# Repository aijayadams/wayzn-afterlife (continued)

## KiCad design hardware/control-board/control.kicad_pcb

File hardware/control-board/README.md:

# Phase B: wayzn-afterlife control board v1 (WYP-BC-100 replacement)

A drop-in replacement for the Wayzn WYP-BC-100 control board: same 33.94 × 152.6 mm outline, the same four post
holes, and J6/J7/J2/J5 and the door button where Wayzn's are, so the door's cables, the shell's posts, the
button cap and the light pipe all line up. The ESP32-C5 drives the motor itself (DRV8876); there is no STM32 and
no imp. Design notes: [docs/CONTROL-BOARD.md](../../docs/CONTROL-BOARD.md). Board geometry:
[docs/hardware/WYP-BC-100-MECHANICAL.md](../../docs/hardware/WYP-BC-100-MECHANICAL.md).

Status: **laid out by hand and checked (ERC, DRC with schematic parity, courtyards, silkscreen: all clean); not
ordered.** Every part has an LCSC number (checked against JLC's library 2026-11-24). The original board stays in
the drawer: going back is just moving the connectors. Ordering: `fab/ORDER.md`.

Pictures: `out/overlay-scan.jpg` (this board's parts on the scan of the Wayzn board), `out/render-top.png`,
`out/render-bottom.png`, `out/plan.png` (pads, nets and routes, 1 mm grid). `out/fit-check-1to1.pdf`: print at
100 % and lay it on the Wayzn board.

## What's on it

| Ref | Part | Notes |
|---|---|---|
| U1 | ESP32-C5-WROOM-1U-N8R8 | Wi-Fi 6 (2.4 + 5 GHz), BLE; runs the door and the motor. U.FL antenna |
| U2 | ESP32-H2-MINI-1U-H4S | Thread RCP; the C5 resets and reflashes it. MHF III antenna |
| U5 | TI DRV8876PWPR | Motor H-bridge. PH/EN mode; IMODE tied low = fixed off-time current chopping, auto-retry, and nFAULT only on real faults (overcurrent, thermal, undervoltage), not on every chop; current mirror on IPROPI |
| U4 + L1 | TI TPS54202 + 10 uH | 12 V → 3.3 V buck, 2 A, 28 V input (above the TVS clamp) |
| D1, D2 | SS54, SMBJ15A | Reverse-polarity diode; 12 V TVS (clamps at 24.4 V) |
| U3 | LIS2DH12 | Accelerometer (optional) |
| J7 / J6 | JST VH 2-pin side entry | 12 V in / motor, in Wayzn's positions (pitch measured 3.96 mm on the scan) |
| J5 / J2 | JST PH 4-pin SMD top entry | Encoder / Grid-EYE: Wayzn pin order, orientation (pin 1 toward the middle) and housing positions |
| SW3 | C&K PTS645VL58 right-angle | The door button, on Wayzn's exact pads (same footprint), so the shell's cap fits its plunger |
| D3 + U6 | WS2812B-2020-V6 RGB LED + HT7536-1 3.6 V LDO | Addressable status LED under the shell's light pipe, one data line from the C5 (RMT). Its own 3.6 V supply from VM keeps it inside its 3.3–5.3 V rating; its data threshold (0.55 × VDD = 2.04 V worst case) leaves 1.2 V margin from 3.3 V logic. Limit brightness in firmware: the LDO dissipates ~0.3 W at full white |
| H1–H4 | NPTH 4.3 mm | The shell posts (Wayzn's holes are ~4.0; 0.3 mm slack for the scan's scale error) |
| R27, R28 | 100 k, 0 Ω (not fitted) | LED data pull-down (no random colour during reset); R28 is a fallback that runs the LED from 3V3 instead of U6 |
| J1, SW1, SW2, JP1 | 1x6 header, RESET, BOOT, bench-3V3 jumper | Programming, as on the carrier |

## Motor drive and safety (hardware side)

- **Current cap: 1.10 A** in hardware: VREF = 3V3, R_IPROPI = 3.0 k (ITRIP = 3.3 V / (1000 uA/A × 3.0 k)). Wayzn
  caps at 1.03 A; normal moves draw ~0.4 A and the most seen was 0.75 A. Firmware can't exceed it.
- **Motor off by default:** nSLEEP, EN and PH have 10 k pull-downs, and none of them is on a C5 strapping pin, so
  reset, boot, flashing or a brownout can't move the motor.
- **Current sense:** IPROPI → 1 k / 10 nF → C5 ADC (GPIO6), **3.0 V/A**; readings flatten near the cap. 12 V sense:
  100 k / 10 k → GPIO1 (÷ 11).
- **nFAULT** (overcurrent, thermal, undervoltage) → GPIO7 with a 10 k pull-up.

## C5 pin map

| Module pin (GPIO) | Net | Notes |
|---|---|---|
| 3 (EN) | C5_EN | 10 k / 1 u, RESET, J1 |
| 4 (2) / 5 (3) | H2_BOOT / H2_EN | open-drain to the H2 |
| 7 (1) | VM_ADC | ADC1_CH0, 12 V ÷ 11 |
| 8 (6) | IPROPI_ADC | ADC1_CH5, motor current 3.0 V/A |
| 9 (7) | DRV_NFAULT | input, 10 k pull-up; also an MCPWM fault input. Strap (JTAG source, no internal pull): the pull-up defines it |
| 10 (8) / 11 (9) / 12 (10) | DRV_NSLEEP / DRV_PH / DRV_EN | 10 k pull-downs; EN = PWM (MCPWM) |
| 13 (13) / 14 (14) | H2_TXD / H2_RXD | H2 UART (C5 RX / TX); native USB not used |
| 15 (28) | C5_BOOT | strap, BOOT, J1 |
| 16 (5) / 17 (4) | ENC_B / ENC_A | PCNT quadrature, 10 k pull-ups + 100 R / 1 nF |
| 18 (27) | I2C_SDA | strap: must be high at reset for UART download (Joint Download Boot 0); the 4.7 k pull-up does it |
| 21 (23) | ACC_INT1 | |
| 23 (24) | I2C_SCL | Grid-EYE + LIS2DH12 share the bus, 4.7 k pull-ups |
| 24 (12) / 25 (11) | C5_RXD0 / C5_TXD0 | J1 |
| 26 (25) / 27 (26) | LED_STATUS / BTN | WS2812 data (RMT); button 10 k pull-up + 100 n |
| 6 (0), 19 (15) | spare / PSRAM CS (must stay unconnected) | |

## Programming

As on the carrier: J1 (pin names on the back) 3V3\*, GND, EN, TXO, RXI, BOOT. Hold BOOT, tap RESET, flash. J1
pin 1 is connected only if JP1 is bridged: bench flashing with the board out of the door only.

## Layout

Placement, every route and every silkscreen label are in `layout.py`, in the scan frame (component side, J6/J7 end
at the top). Power and motor section at the J6/J7 end (0.8 mm tracks for 12 V and the motor; OUT1 returns on the
bottom layer through 0.8/0.4 vias). The C5 in the middle; its left pins run to the driver in one uncrossed lane (pull
resistors as tees at 2 mm pitch), its right pins go up to the button, LED and J1 and down to the encoder, the
accelerometer and the Grid-EYE. The H2 below it, programming buttons lower left. 4 layers: F signals + GND,
In1 GND, In2 3V3, B signals + GND; GND stitching on a 3 mm grid.

KiCad reports courtyard overlaps as warnings: `gen_pcb.check_overlaps` checks them instead, with two documented
exceptions (the VH housings 0.84 mm apart, as on Wayzn's board; the posts have no screw heads).

**Don't edit `control.kicad_pcb` in KiCad and expect it to stick:** `build.sh` regenerates it. Change `design.py`
or `layout.py` and rebuild. Needs KiCad 10.

## Files

`design.py` (parts, nets, rules), `layout.py`, `build.sh`, `gen_sch.py`, `gen_pcb.py`, `route.py` (fanout,
stitching), `mk_sym.py` (LIS2DH12, DRV8876 symbols), `fab.py` (JLC Gerbers/BOM/CPL), `order.py`
(`fab/order-bom.csv`), `padmap.py`, `planplot.py`, `overlay.py` (needs `out/boxes.json`, see its docstring).

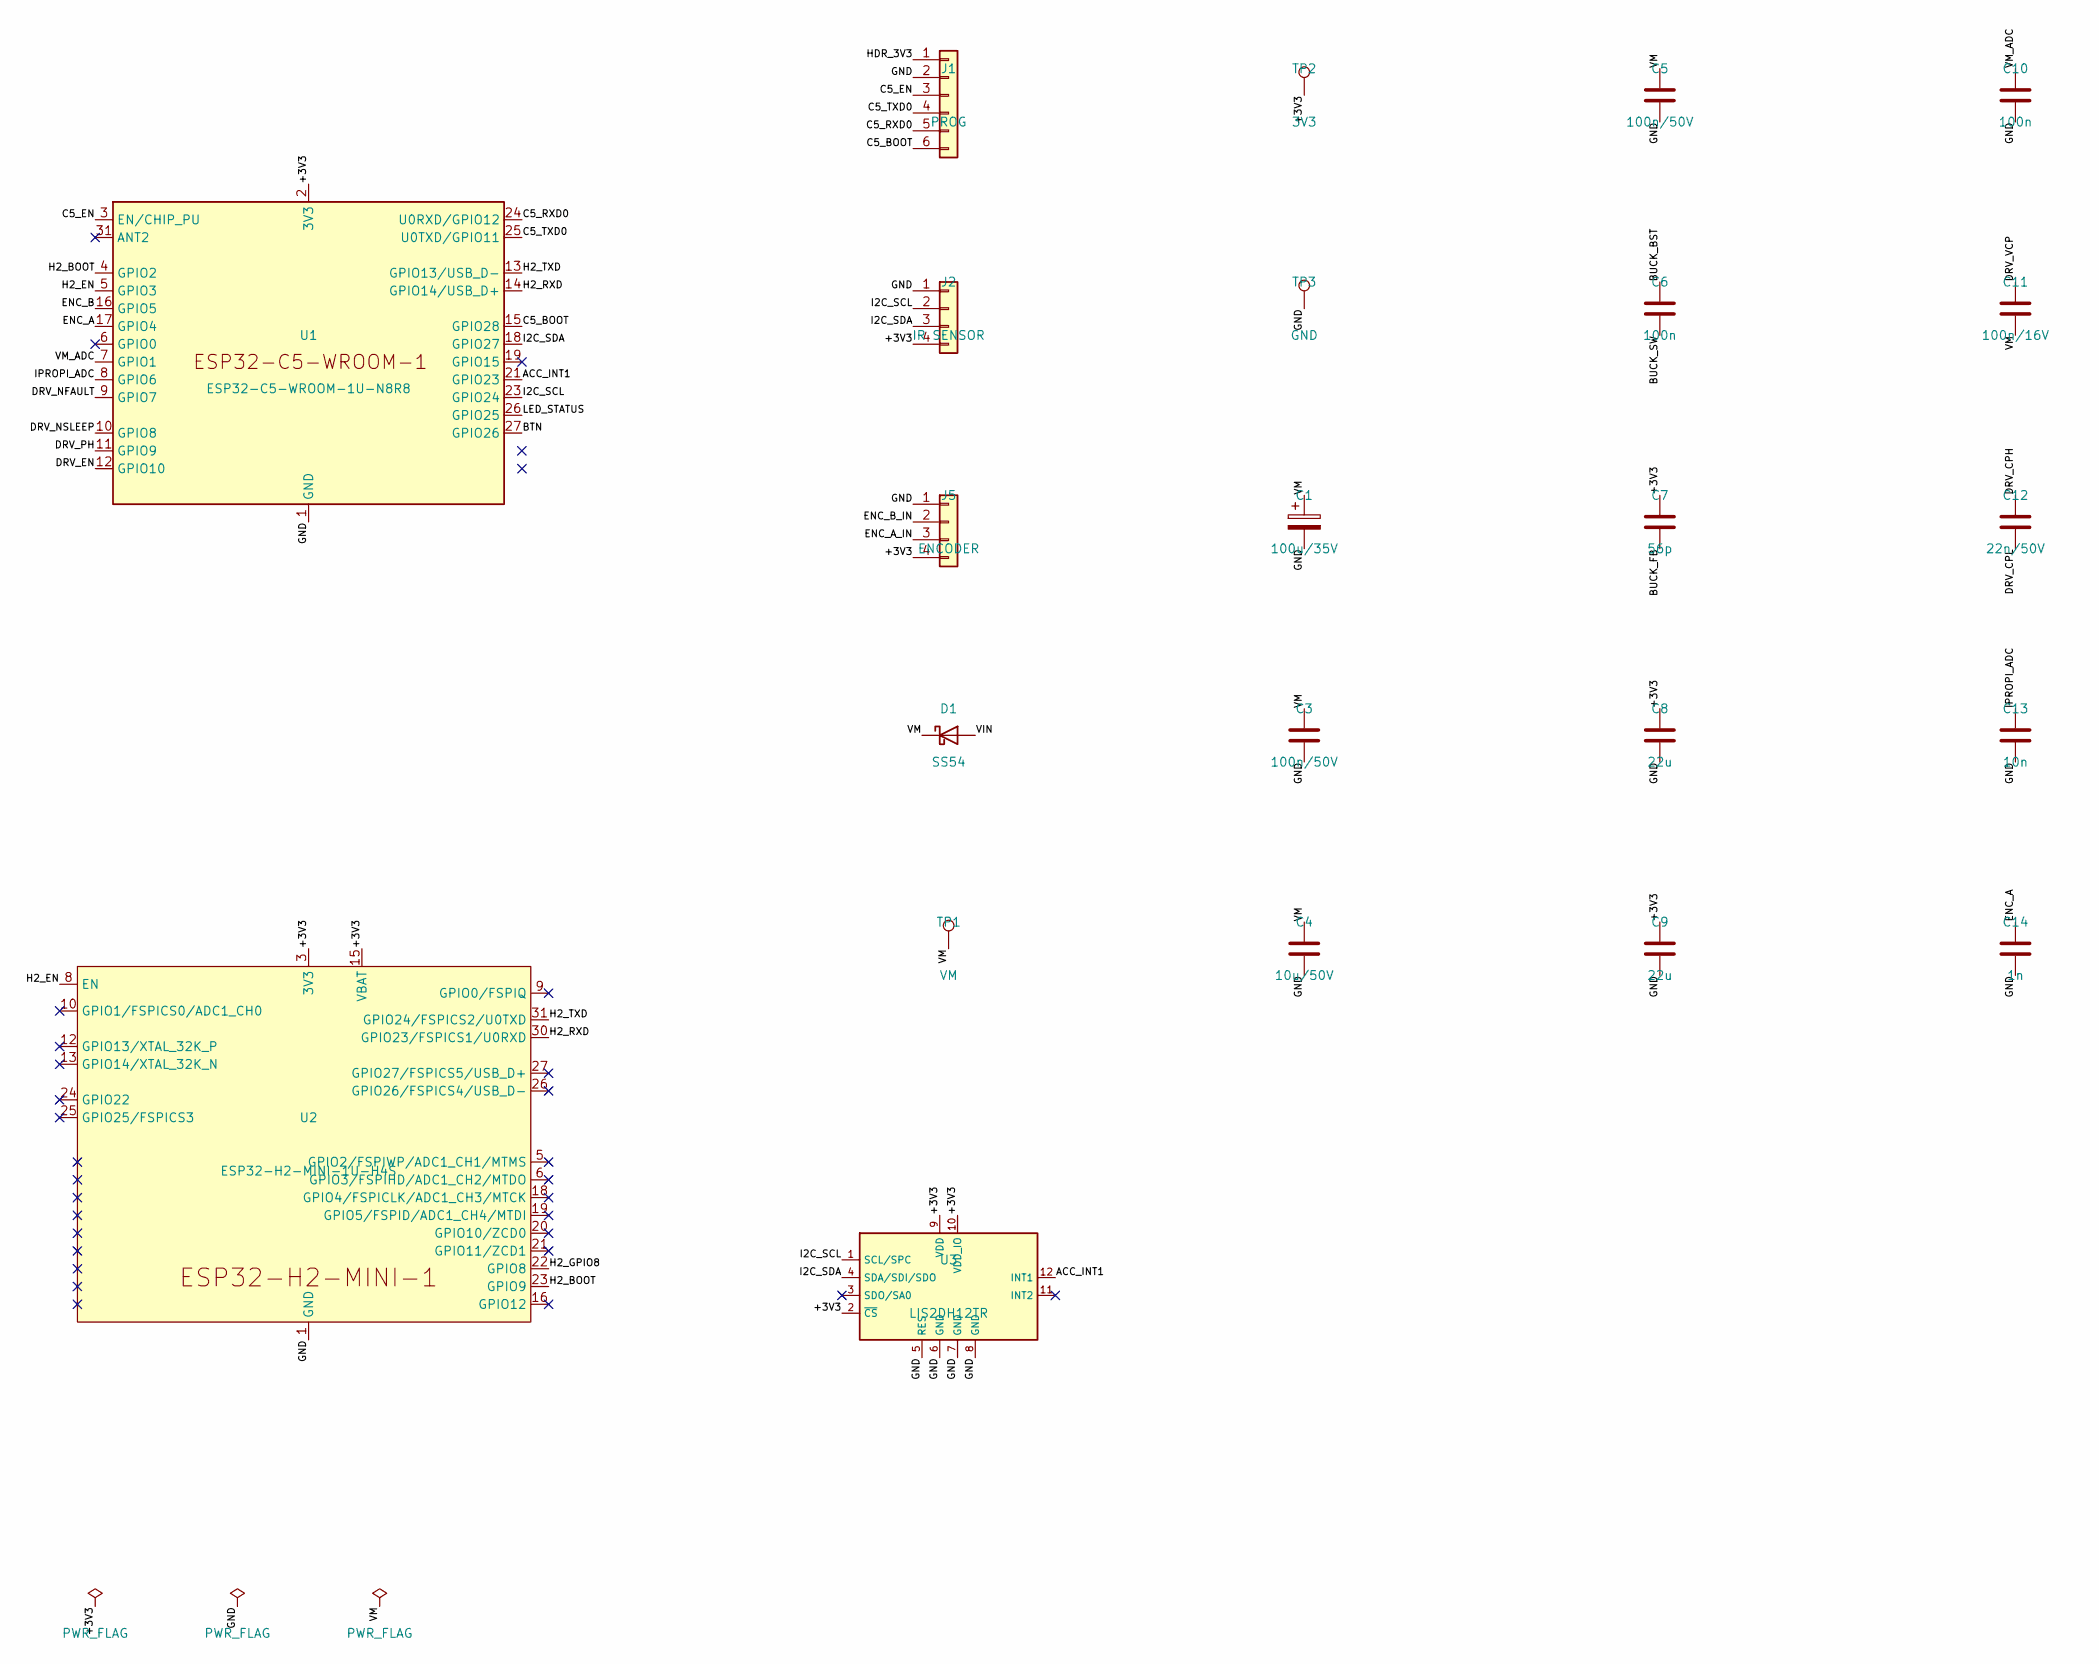
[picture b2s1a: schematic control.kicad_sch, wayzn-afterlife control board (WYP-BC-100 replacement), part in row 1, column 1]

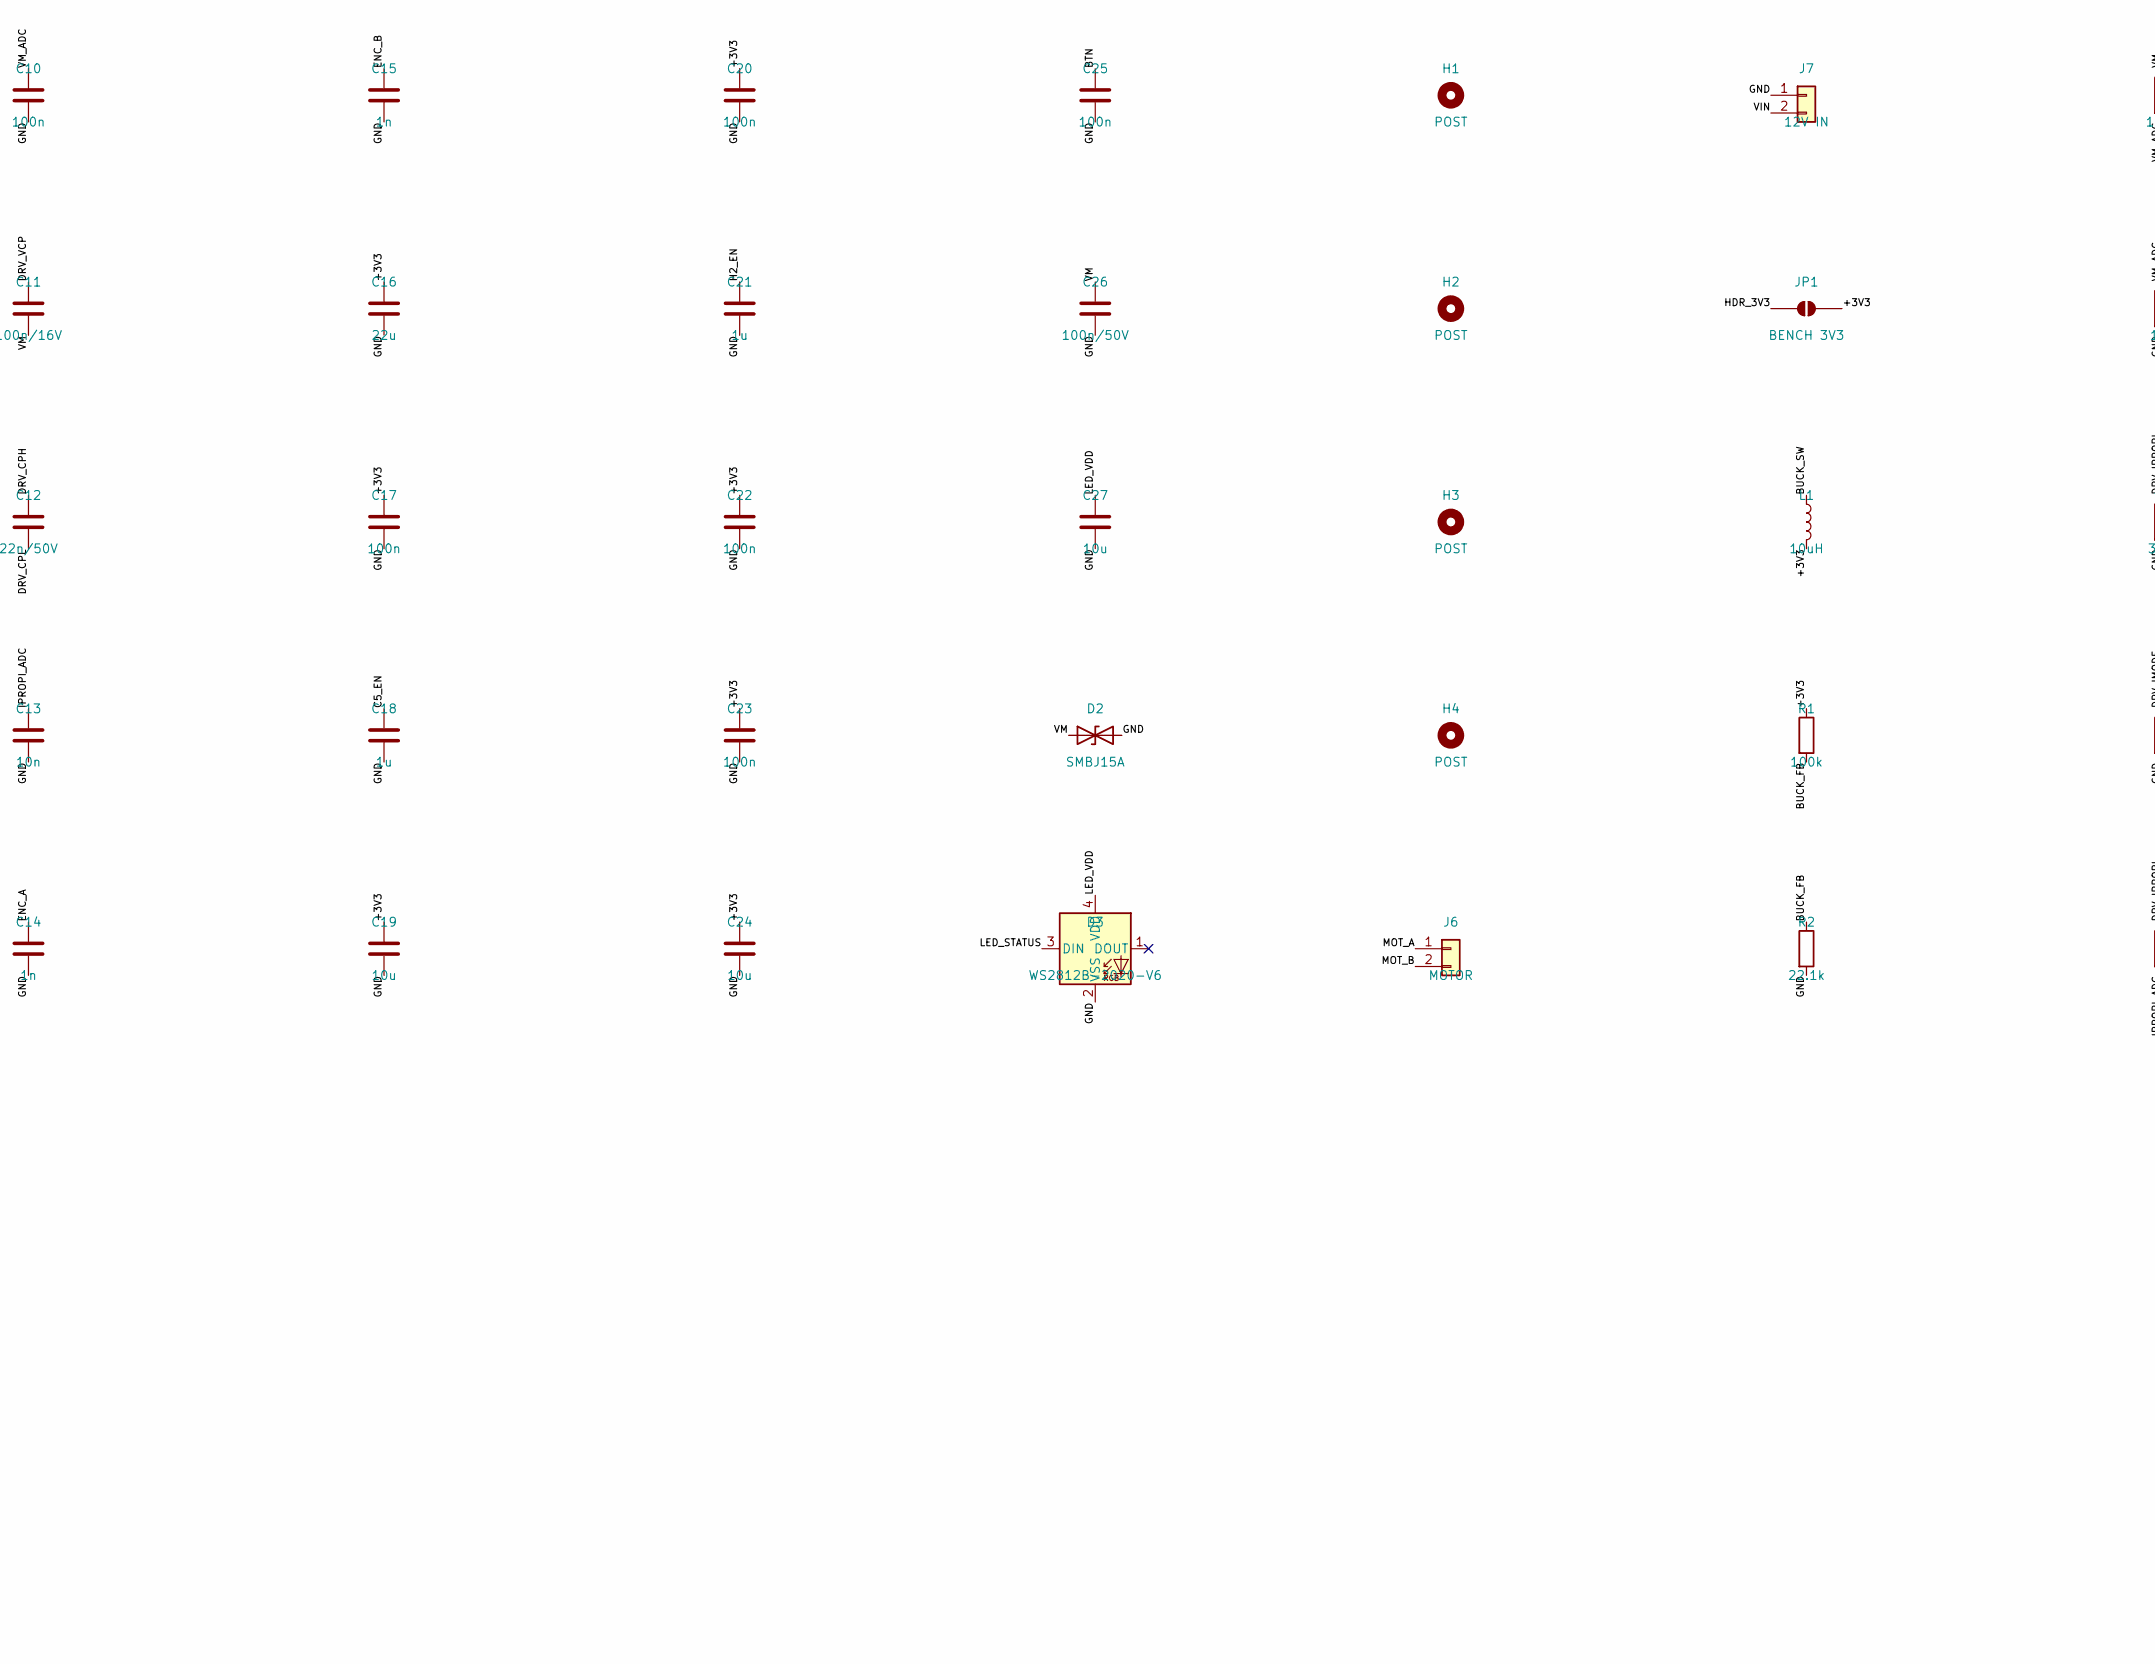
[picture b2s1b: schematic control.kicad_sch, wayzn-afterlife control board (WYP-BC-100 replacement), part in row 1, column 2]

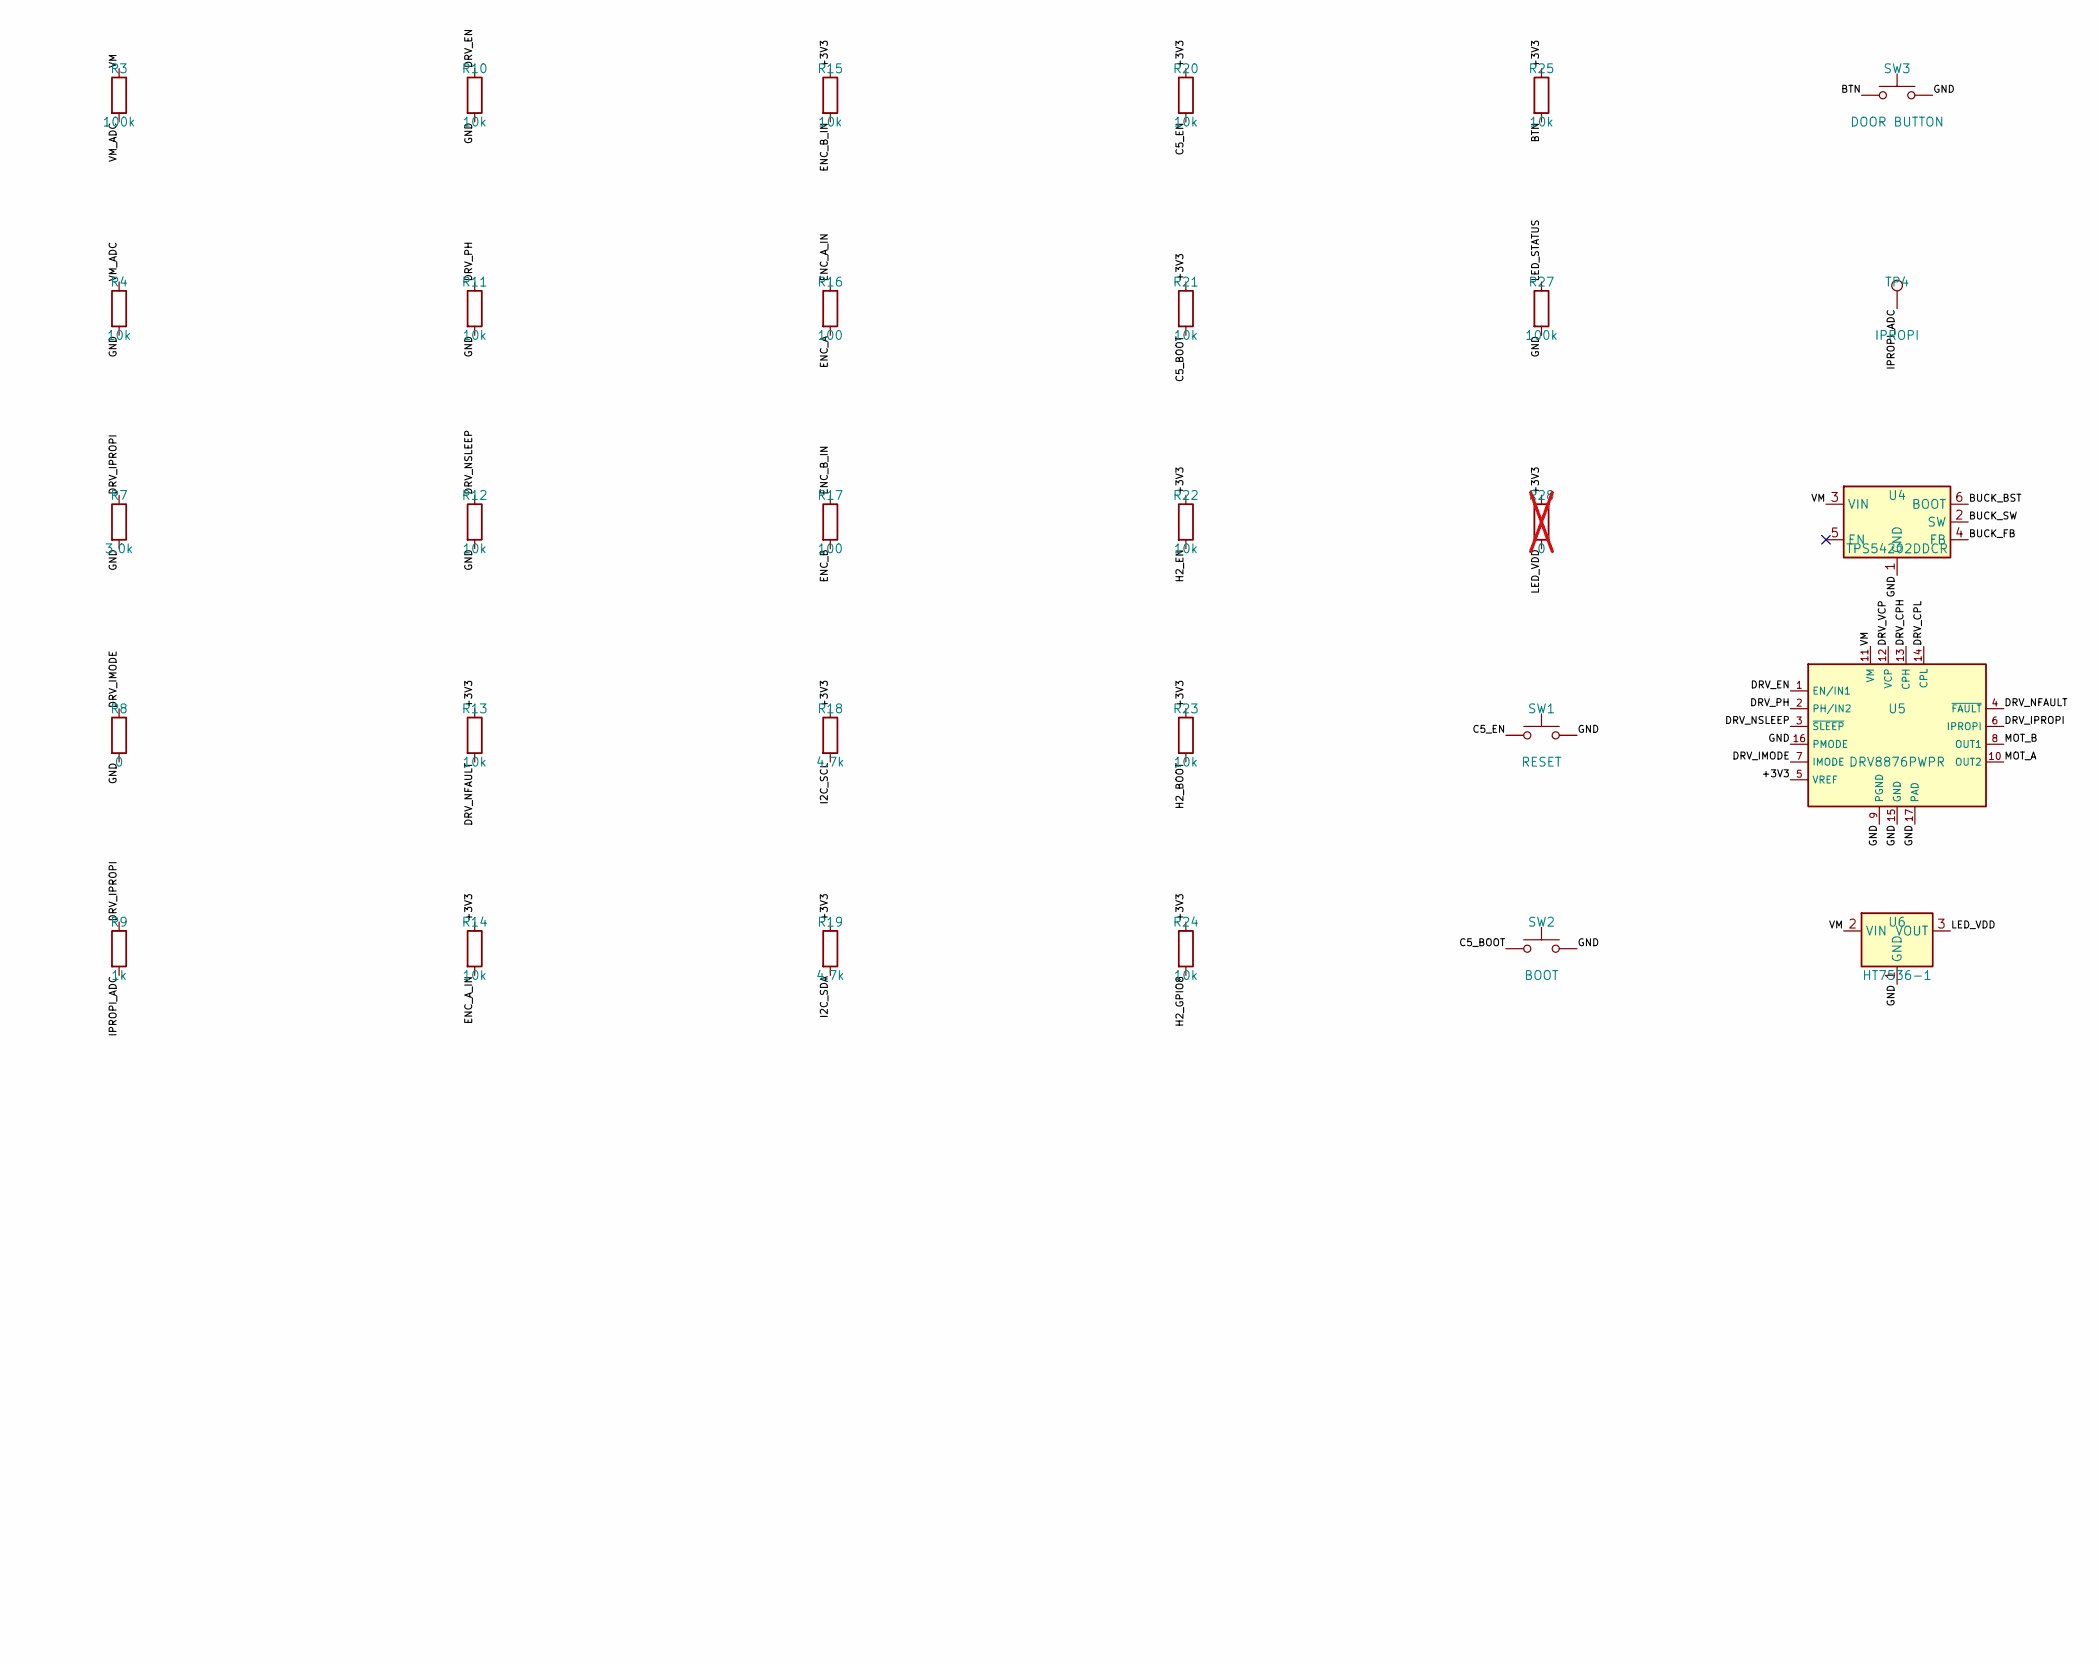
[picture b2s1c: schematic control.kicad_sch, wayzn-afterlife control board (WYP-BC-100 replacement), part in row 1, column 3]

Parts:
C1: 100u/35V; CP_Elec_6.3x7.7; LCSC C125975
C3, C5, C26: 100n/50V; C_0603_1608Metric; LCSC C149620
C4: 10u/50V; C_1206_3216Metric; LCSC C13585
C6, C10, C17, C20, C22, C23, C25: 100n; C_0402_1005Metric; LCSC C1525
C7: 56p; C_0402_1005Metric; LCSC C1572
C8, C9, C16: 22u; C_0805_2012Metric; LCSC C45783
C11: 100n/16V; C_0402_1005Metric; LCSC C1525
C12: 22n/50V; C_0603_1608Metric; LCSC C21122
C13: 10n; C_0402_1005Metric; LCSC C15195
C14, C15: 1n; C_0402_1005Metric; LCSC C1523
C18, C21: 1u; C_0402_1005Metric; LCSC C52923
C19, C24, C27: 10u; C_0603_1608Metric; LCSC C96446
D1: SS54; D_SMA; LCSC C22452
D2: SMBJ15A; D_SMB; LCSC C188412
D3: WS2812B-2020-V6; LED_WS2812B-2020_PLCC4_2.0x2.0mm; LCSC C52917434
H1, H2, H3, H4: POST; MountingHole_4.3mm_M4
J1: PROG; PinHeader_1x06_P2.54mm_Vertical
J2: IR SENSOR; JST_PH_B4B-PH-SM4-TB_1x04-1MP_P2.00mm_Vertical; LCSC C160354
J5: ENCODER; JST_PH_B4B-PH-SM4-TB_1x04-1MP_P2.00mm_Vertical; LCSC C160354
J6: MOTOR; JST_VH_B2PS-VH_1x02_P3.96mm_Horizontal; LCSC C158007
J7: 12V IN; JST_VH_B2PS-VH_1x02_P3.96mm_Horizontal; LCSC C158007
JP1: BENCH 3V3; SolderJumper-2_P1.3mm_Open_RoundedPad1.0x1.5mm
L1: 10uH; L_Sunlord_SWPA6045S; LCSC C79272
R1, R3, R27: 100k; R_0402_1005Metric; LCSC C25741
R2: 22.1k; R_0402_1005Metric; LCSC C43473
R4, R10, R11, R12, R13, R14, R15, R20, R21, R22, R23, R24, R25: 10k; R_0402_1005Metric; LCSC C25744
R7: 3.0k; R_0402_1005Metric; LCSC C25784
R8: 0; R_0402_1005Metric; LCSC C17168
R9: 1k; R_0402_1005Metric; LCSC C11702
R16, R17: 100; R_0402_1005Metric; LCSC C25076
R18, R19: 4.7k; R_0402_1005Metric; LCSC C25900
R28: 0; R_0402_1005Metric; LCSC C17168; not fitted
SW1: RESET; SW_Push_1P1T_XKB_TS-1187A; LCSC C318884
SW2: BOOT; SW_Push_1P1T_XKB_TS-1187A; LCSC C318884
SW3: DOOR BUTTON; SW_Tactile_SPST_Angled_PTS645Vx58-2LFS; LCSC C285524
TP1: VM; TestPoint_Pad_D1.5mm
TP2: 3V3; TestPoint_Pad_D1.5mm
TP3: GND; TestPoint_Pad_D1.5mm
TP4: IPROPI; TestPoint_Pad_D1.5mm
U1: ESP32-C5-WROOM-1U-N8R8; ESP32-C5-WROOM-1U; LCSC C51950748
U2: ESP32-H2-MINI-1U-H4S; ESP32-H2-MINI-1U; LCSC C49450282
U3: LIS2DH12TR; LGA-12_2x2mm_P0.5mm; LCSC C110926
U4: TPS54202DDCR; SOT-23-6; LCSC C191884
U5: DRV8876PWPR; HTSSOP-16-1EP_4.4x5mm_P0.65mm_EP3.4x5mm_Mask2.46x2.31mm; LCSC C575551
U6: HT7536-1; SOT-89-3; LCSC C78876

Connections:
/+3V3: C7.1, C8.1, C9.1, C16.1, C17.1, C19.1, C20.1, C22.1, C23.1, C24.1, J2.4, J5.4, JP1.2 (B), L1.2, R1.1, R13.1, R14.1, R15.1, R18.1, R19.1, R20.1, R21.1, R22.1, R23.1, R24.1, R25.1, R28.1, TP2.1, U1.2 (3V3), U2.3 (3V3), U2.15 (VBAT), U3.2 (~CS), U3.9 (VDD), U3.10 (VDD_IO), U5.5 (VREF)
/ACC_INT1: U1.21 (GPIO23), U3.12 (INT1)
/BTN: C25.1, R25.2, SW3.1, U1.27 (GPIO26)
/BUCK_BST: C6.1, U4.6 (BOOT)
/BUCK_FB: C7.2, R1.2, R2.1, U4.4 (FB)
/BUCK_SW: C6.2, L1.1, U4.2 (SW)
/C5_BOOT: J1.6, R21.2, SW2.1, U1.15 (GPIO28)
/C5_EN: C18.1, J1.3, R20.2, SW1.1, U1.3 (EN/CHIP_PU)
/C5_RXD0: J1.5, U1.24 (U0RXD/GPIO12)
/C5_TXD0: J1.4, U1.25 (U0TXD/GPIO11)
/DRV_CPH: C12.1, U5.13 (CPH)
/DRV_CPL: C12.2, U5.14 (CPL)
/DRV_EN: R10.1, U1.12 (GPIO10), U5.1 (EN/IN1)
/DRV_IMODE: R8.1, U5.7 (IMODE)
/DRV_IPROPI: R7.1, R9.1, U5.6 (IPROPI)
/DRV_NFAULT: R13.2, U1.9 (GPIO7), U5.4 (~FAULT)
/DRV_NSLEEP: R12.1, U1.10 (GPIO8), U5.3 (~SLEEP)
/DRV_PH: R11.1, U1.11 (GPIO9), U5.2 (PH/IN2)
/DRV_VCP: C11.1, U5.12 (VCP)
/ENC_A: C14.1, R16.2, U1.17 (GPIO4)
/ENC_A_IN: J5.3, R14.2, R16.1
/ENC_B: C15.1, R17.2, U1.16 (GPIO5)
/ENC_B_IN: J5.2, R15.2, R17.1
/GND: C1.2, C3.2, C4.2, C5.2, C8.2, C9.2, C10.2, C13.2, C14.2, C15.2, C16.2, C17.2, C18.2, C19.2, C20.2, C21.2, C22.2, C23.2, C24.2, C25.2, C26.2, C27.2, D2.2 (A2), D3.2 (VSS), J1.2, J2.1, J5.1, J7.1, R2.2, R4.2, R7.2, R8.2, R10.2, R11.2, R12.2, R27.2, SW1.2, SW2.2, SW3.2, TP3.1, U1.1 (GND), U1.28 (GND), U1.29 (GND), U1.30 (GND), U1.32 (GND), U2.1 (GND), U2.2 (GND), U2.11 (GND), U2.14 (GND), U2.36 (GND), U2.37 (GND), U2.38 (GND), U2.39 (GND), U2.40 (GND), U2.41 (GND), U2.42 (GND), U2.43 (GND), U2.44 (GND), U2.45 (GND), U2.46 (GND), U2.47 (GND), U2.48 (GND), U2.49 (GND), U2.50 (GND), U2.51 (GND), U2.52 (GND), U2.53 (GND), U3.5 (RES), U3.6 (GND), U3.7 (GND), U3.8 (GND), U4.1 (GND), U5.9 (PGND), U5.15 (GND), U5.16 (PMODE), U5.17 (PAD), U6.1 (GND)
/H2_BOOT: R23.2, U1.4 (GPIO2), U2.23 (GPIO9)
/H2_EN: C21.1, R22.2, U1.5 (GPIO3), U2.8 (EN)
/H2_GPIO8: R24.2, U2.22 (GPIO8)
/H2_RXD: U1.14 (GPIO14/USB_D+), U2.30 (GPIO23/FSPICS1/U0RXD)
/H2_TXD: U1.13 (GPIO13/USB_D-), U2.31 (GPIO24/FSPICS2/U0TXD)
/HDR_3V3: J1.1, JP1.1 (A)
/I2C_SCL: J2.2, R18.2, U1.23 (GPIO24), U3.1 (SCL/SPC)
/I2C_SDA: J2.3, R19.2, U1.18 (GPIO27), U3.4 (SDA/SDI/SDO)
/IPROPI_ADC: C13.1, R9.2, TP4.1, U1.8 (GPIO6)
/LED_STATUS: D3.3 (DIN), R27.1, U1.26 (GPIO25)
/LED_VDD: C27.1, D3.4 (VDD), R28.2, U6.3 (VOUT)
/MOT_A: J6.1, U5.10 (OUT2)
/MOT_B: J6.2, U5.8 (OUT1)
/VIN: D1.2 (A), J7.2
/VM: C1.1, C3.1, C4.1, C5.1, C11.2, C26.1, D1.1 (K), D2.1 (A1), R3.1, TP1.1, U4.3 (VIN), U5.11 (VM), U6.2 (VIN)
/VM_ADC: C10.1, R3.2, R4.1, U1.7 (GPIO1)

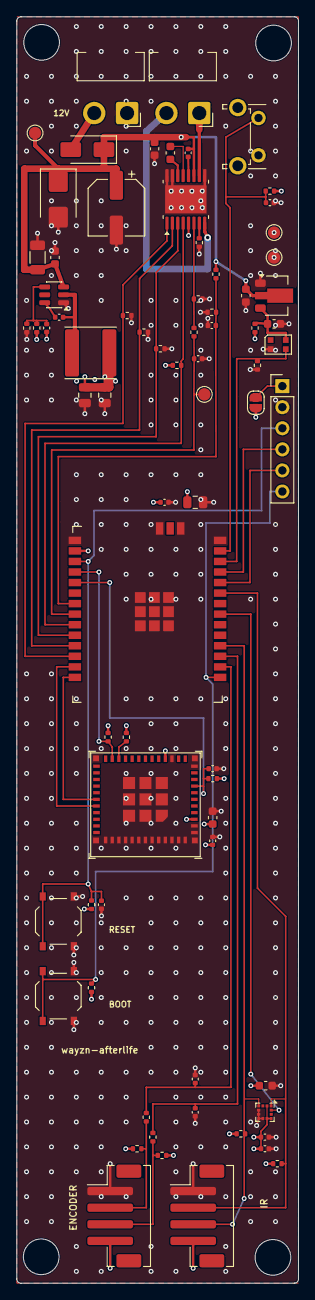
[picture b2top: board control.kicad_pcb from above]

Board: 4 copper layers, 33.9 x 152.6 mm, 78 parts (0 on the bottom side), 40 nets.

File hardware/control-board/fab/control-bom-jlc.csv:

Comment,Designator,Footprint,LCSC
100u/35V,C1,CP_Elec_6.3x7.7,C125975
100n/16V,C11,C_0402_1005Metric,C1525
22n/50V,C12,C_0603_1608Metric,C21122
10n,C13,C_0402_1005Metric,C15195
1n,"C14,C15",C_0402_1005Metric,C1523
1u,"C18,C21",C_0402_1005Metric,C52923
10u,"C19,C24,C27",C_0603_1608Metric,C96446
100n/50V,"C3,C5,C26",C_0603_1608Metric,C149620
10u/50V,C4,C_1206_3216Metric,C13585
100n,"C6,C10,C17,C20,C22,C23,C25",C_0402_1005Metric,C1525
56p,C7,C_0402_1005Metric,C1572
22u,"C8,C9,C16",C_0805_2012Metric,C45783
SS54,D1,D_SMA,C22452
SMBJ15A,D2,D_SMB,C188412
IR SENSOR,J2,JST_PH_B4B-PH-SM4-TB_1x04-1MP_P2.00mm_Vertical,C160354
ENCODER,J5,JST_PH_B4B-PH-SM4-TB_1x04-1MP_P2.00mm_Vertical,C160354
10uH,L1,L_Sunlord_SWPA6045S,C79272
100k,"R1,R3,R27",R_0402_1005Metric,C25741
100,"R16,R17",R_0402_1005Metric,C25076
4.7k,"R18,R19",R_0402_1005Metric,C25900
22.1k,R2,R_0402_1005Metric,C43473
10k,"R4,R10,R11,R12,R13,R14,R15,R20,R21,R22,R23,R24,R25",R_0402_1005Metric,C25744
3.0k,R7,R_0402_1005Metric,C25784
0,R8,R_0402_1005Metric,C17168
1k,R9,R_0402_1005Metric,C11702
RESET,SW1,SW_Push_1P1T_XKB_TS-1187A,C318884
BOOT,SW2,SW_Push_1P1T_XKB_TS-1187A,C318884
LIS2DH12TR,U3,LGA-12_2x2mm_P0.5mm,C110926
TPS54202DDCR,U4,SOT-23-6,C191884
DRV8876PWPR,U5,HTSSOP-16-1EP_4.4x5mm_P0.65mm_EP3.4x5mm_Mask2.46x2.31mm,C575551
HT7536-1,U6,SOT-89-3,C78876

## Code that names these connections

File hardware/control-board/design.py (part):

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    # --- radios / MCU
    "U1": ("Espressif:ESP32-C5-WROOM-1U", "Espressif:ESP32-C5-WROOM-1U", "ESP32-C5-WROOM-1U-N8R8", "C51950748",
           "main MCU and motor controller: Wi-Fi 6 dual band, BLE 5; U.FL antenna (2.4/5 GHz)",
           # The outputs that can move the motor (EN, nSLEEP, PH) avoid the strapping pins (MTMS/GPIO2, GPIO7,
           # GPIO27, GPIO28) and have external pull-downs, so reset and boot can never drive the bridge. Left-side
           # order (EN, PH, nSLEEP, nFAULT, then the two ADCs, bottom to top) matches the DRV8876's pin order, so
           # the six lines reach it without crossing.
           {"1": G, "2": V, "3": "C5_EN",
            "4": "H2_BOOT",                        # GPIO2 (MTMS: listed as a strap, no boot function): to H2 GPIO9
            "5": "H2_EN",                          # GPIO3: open-drain, resets the H2
            "6": None,                             # GPIO0: spare
            "7": "VM_ADC",                         # GPIO1 = ADC1_CH0: 12 V rail / 11
            "8": "IPROPI_ADC",                     # GPIO6 = ADC1_CH5: motor current, 3.0 V/A
            "9": "DRV_NFAULT",                     # GPIO7 (strap: JTAG source; no internal pull, so it must be
                                                   # driven at reset: the 10k pull-up does it): input
            "10": "DRV_NSLEEP",                    # GPIO8: driver enable, 10k pull-down (asleep at reset)
            "11": "DRV_PH",                        # GPIO9: direction, 10k pull-down
            "12": "DRV_EN",                        # GPIO10: PWM to EN/IN1, 10k pull-down
            "13": "H2_TXD",                        # GPIO13 (USB D-) <- H2 U0TXD (RCP UART, C5 RX)
            "14": "H2_RXD",                        # GPIO14 (USB D+) -> H2 U0RXD
            "15": "C5_BOOT",                       # GPIO28: boot strap
            "16": "ENC_B",                         # GPIO5: PCNT
            "17": "ENC_A",                         # GPIO4: PCNT
            "18": "I2C_SDA",                       # GPIO27 (strap): must be HIGH at reset for UART download
                                                   # (Joint Download Boot 0 = GPIO27 1, GPIO28 0): the 4.7k
                                                   # I2C pull-up holds it high. (INT1 here would idle low.)
            "19": None,                            # GPIO15 = PSRAM SPICS1: must stay unconnected
            "20": None, "22": None,
            "21": "ACC_INT1",                      # GPIO23
            "23": "I2C_SCL",                       # GPIO24
            "24": "C5_RXD0", "25": "C5_TXD0",      # UART0, programming header
            "26": "LED_STATUS",                    # GPIO25 (SDIO-timing strap only)
            "27": "BTN",                           # GPIO26 (download-only strap; idles high via its pull-up)
            "28": G, "29": G, "30": G, "31": None, "32": G}),
    "U2": ("Espressif:ESP32-H2-MINI-1", "Espressif:ESP32-H2-MINI-1U", "ESP32-H2-MINI-1U-H4S", "C49450282",
           "Thread radio (OpenThread RCP on UART0); the C5 resets and reflashes it. MHF III antenna socket",
           dict({"3": V, "15": V,
                 "8": "H2_EN", "23": "H2_BOOT", "22": "H2_GPIO8",
                 "30": "H2_RXD", "31": "H2_TXD",
                 "26": None, "27": None},
                **{p: None for p in ("4", "5", "6", "7", "9", "10", "12", "13", "16", "17", "18", "19", "20",
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           "C160354", "motor encoder, Wayzn pin order: GND, SIG B, SIG A, 3V3",
           {"1": G, "2": "ENC_B_IN", "3": "ENC_A_IN", "4": V, "MP": None}),
    "J2": ("Connector_Generic:Conn_01x04", "Connector_JST:JST_PH_B4B-PH-SM4-TB_1x04-1MP_P2.00mm_Vertical", "IR SENSOR",
           "C160354", "Grid-EYE, Wayzn pin order: GND, SCL, SDA, 3V3", {"1": G, "2": "I2C_SCL", "3": "I2C_SDA", "4": V,
                                                                      "MP": None}),
    "J1": ("Connector_Generic:Conn_01x06", "Connector_PinHeader_2.54mm:PinHeader_1x06_P2.54mm_Vertical", "PROG", "",
           "UART programming: 3V3* (via JP1 only), GND, EN, TXO, RXI, BOOT",
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    "SW1": ("Switch:SW_Push", "Button_Switch_SMD:SW_Push_1P1T_XKB_TS-1187A", "RESET", "C318884", "C5 EN",
            {"1": "C5_EN", "2": G}),
    "SW2": ("Switch:SW_Push", "Button_Switch_SMD:SW_Push_1P1T_XKB_TS-1187A", "BOOT", "C318884",
            "C5 GPIO28: hold while pressing RESET for download mode", {"1": "C5_BOOT", "2": G}),
    "SW3": ("Switch:SW_Push", "Button_Switch_THT:SW_Tactile_SPST_Angled_PTS645Vx58-2LFS", "DOOR BUTTON", "C285524",
            "C&K PTS645VL58 right-angle, in Wayzn's switch position (the same footprint): the shell's cap fits its "
            "plunger", {"1": "BTN", "2": G}),
    "D3": ("LED:WS2812B-2020", "LED_SMD:LED_WS2812B-2020_PLCC4_2.0x2.0mm", "WS2812B-2020-V6", "C52917434",
           "addressable RGB status LED under the shell's light pipe (C5 RMT on GPIO25). V6: VDD 3.3-5.3 V, "
           "VIH 0.55 x VDD (2.04 V at the LDO's 3.71 V maximum: 1.2 V margin from 3.3 V logic)",
           {"1": None, "2": G, "3": "LED_STATUS", "4": "LED_VDD"}),
    "U6": ("Regulator_Linear:HT75xx-1-SOT89", "Package_TO_SOT_SMD:SOT-89-3", "HT7536-1", "C78876",
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}

# LIS2DH12 (LGA-12), ST DocID025056 Rev 6 Table 2: I2C mode needs CS high; SA0 open (internal pull-up) = 0x19.
PIN_U3 = {"1": "I2C_SCL", "2": V, "3": None, "4": "I2C_SDA", "5": G, "6": G, "7": G, "8": G,
          "9": V, "10": V, "11": None, "12": "ACC_INT1"}

R0402, C0402 = "Resistor_SMD:R_0402_1005Metric", "Capacitor_SMD:C_0402_1005Metric"
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    ("C12", "C", "22n/50V", C0603, "DRV_CPH", "DRV_CPL", "DRV8876 charge-pump flying cap (VM rated)"),
    ("R7", "R", "3.0k", R0402, "DRV_IPROPI", G, "IPROPI: 1000 uA/A x 3.0k = 3.0 V/A; trips at VREF = 3.3 V "
     "(1.10 A). At the C5 end of the line: the DRV8876 compares the pin voltage, so position doesn't matter"),
    ("R8", "R", "0", R0402, "DRV_IMODE", G, "IMODE tied low: fixed off-time chopping, auto-retry"),
    ("R9", "R", "1k", R0402, "DRV_IPROPI", "IPROPI_ADC", "IPROPI to ADC, RC filter"),
    ("C13", "C", "10n", C0402, "IPROPI_ADC", G, "IPROPI ADC filter (1k/10n: 16 kHz)"),
    ("R10", "R", "10k", R0402, "DRV_EN", G, "EN pull-down: motor off at reset"),
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    ("C17", "C", "100n", C0402, V, G, "C5 decoupling"),
    ("R20", "R", "10k", R0402, V, "C5_EN", "C5 EN pull-up (10k/1u)"),
    ("C18", "C", "1u", C0402, "C5_EN", G, "C5 EN delay"),
    ("R21", "R", "10k", R0402, V, "C5_BOOT", "C5 GPIO28 strap pull-up"),
    # H2
    ("C19", "C", "10u", C0603, V, G, "H2 bulk"),
    ("C20", "C", "100n", C0402, V, G, "H2 decoupling"),
    ("R22", "R", "10k", R0402, V, "H2_EN", "H2 EN pull-up"),
    ("C21", "C", "1u", C0402, "H2_EN", G, "H2 EN delay"),
    ("R23", "R", "10k", R0402, V, "H2_BOOT", "H2 GPIO9 strap pull-up"),
    ("R24", "R", "10k", R0402, V, "H2_GPIO8", "H2 GPIO8 pull-up (download mode needs it high)"),
    # accelerometer
    ("C22", "C", "100n", C0402, V, G, "accelerometer VDD"),
    ("C23", "C", "100n", C0402, V, G, "accelerometer VDD_IO"),
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
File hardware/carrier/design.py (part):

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           # Pins chosen so no two routes cross. Left edge (pins 1..14, top to bottom) faces the programming
           # zone; right edge (pins 28..15, top to bottom) faces J1 (STM), the I2C parts and the H2.
           {"1": G, "2": V, "3": "C5_EN",
            "4": "STM_NRST",                       # GPIO2: open-drain, pulls the STM32 reset (100 R series, J4)
            "5": "LED_STATUS",                     # GPIO3 (MTDI strap: SDIO timing only, unused here)
            "6": None, "7": None, "8": None,       # GPIO0, GPIO1, GPIO6: unused
            "9": None, "10": None,                 # GPIO7 (JTAG-select strap), GPIO8: unused
            "11": "H2_BOOT",                       # GPIO9: open-drain, holds H2 GPIO9 low (download mode)
            "12": "H2_EN",                         # GPIO10: open-drain, resets the H2
            "13": None, "14": None,                # GPIO13/14 (native USB D-/D+): unused, kept free
            "15": "C5_BOOT",                       # GPIO28: boot strap (10k pull-up, BOOT button, header)
            "16": "H2_TXD",                        # GPIO5 <- H2 U0TXD (RCP UART, C5 RX)
            "17": "H2_RXD",                        # GPIO4 -> H2 U0RXD (RCP UART, C5 TX)
            "18": "ACC_INT1",                      # GPIO27 (strap): LIS2DH12 INT1 idles low, which only selects
                                                   # download variant 1 instead of 0; UART download works in both
            "19": None,                            # SPICS1 of the in-package PSRAM: must stay unconnected
            "20": None, "22": None,
            "21": "I2C_SCL",                       # GPIO23 (SCL below SDA here, so the two reach J2 uncrossed)
            "23": "I2C_SDA",                       # GPIO24
            "24": "C5_RXD0", "25": "C5_TXD0",      # GPIO12/11: UART0, to the header
            "26": "STM_TX",                        # GPIO25 <- STM32 PA9 (USART1 TX); UART1 RX. Strap: SDIO edge only
            "27": "STM_RX",                        # GPIO26 -> STM32 PA10 (USART1 RX); UART1 TX. Strap: download only
            "28": G, "29": G, "30": G, "31": None, "32": G}),
    "U2": ("Espressif:ESP32-H2-MINI-1", "Espressif:ESP32-H2-MINI-1U", "ESP32-H2-MINI-1U-H4S", "C49450282",
           "Thread/Zigbee radio, OpenThread RCP on UART0 (460800). W.FL (MHF III) antenna socket on the module: "
           "a different pigtail from the C5's",
           dict({"3": V, "15": V,                  # VBAT tied to 3V3
                 "8": "H2_EN", "23": "H2_BOOT",    # GPIO9 = boot strap
                 "22": "H2_GPIO8",                 # strap: must be high for download mode (pull-up)
                 "30": "H2_RXD", "31": "H2_TXD",
                 "26": None, "27": None},                # native USB unused: the C5 reflashes it
                **{p: None for p in ("4", "5", "6", "7", "9", "10", "12", "13", "16", "17", "18", "19", "20",
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    "SW1": ("Switch:SW_Push", "Button_Switch_SMD:SW_Push_1P1T_XKB_TS-1187A", "RESET", "C318884", "C5 EN",
            {"1": "C5_EN", "2": G}),
    "SW2": ("Switch:SW_Push", "Button_Switch_SMD:SW_Push_1P1T_XKB_TS-1187A", "BOOT", "C318884",
            "C5 GPIO28: hold while pressing RESET for download mode", {"1": "C5_BOOT", "2": G}),
    "D1": ("Device:LED", "LED_SMD:LED_0603_1608Metric", "green", "C965804", "status", {"1": "LED_K", "2": "LED_STATUS"}),
}

# LIS2DH12 (LGA-12), ST DocID025056 Rev 6 Table 2: I2C mode needs CS high; SA0 left open (internal pull-up)
# = address 0x19 (firmware must not disable the pull-up via CTRL_REG0); Res (5) to GND; INT2 unused.
PIN_U3 = {"1": "I2C_SCL", "2": V, "3": None, "4": "I2C_SDA", "5": G, "6": G, "7": G, "8": G,
          "9": V, "10": V, "11": None, "12": "ACC_INT1"}

PASSIVES = [
    # ref, kind, value, net on pin 1, net on pin 2, purpose
    ("R1", "R", "10k", V, "C5_EN", "C5 EN pull-up (datasheet RC: 10k / 1u)"),
    ("C1", "C", "1u", "C5_EN", G, "C5 EN delay"),
    ("R2", "R", "10k", V, "C5_BOOT", "C5 GPIO28 strap pull-up (normal boot)"),
    ("R3", "R", "10k", V, "H2_EN", "H2 EN pull-up"),
    ("C2", "C", "1u", "H2_EN", G, "H2 EN delay"),
    ("R4", "R", "10k", V, "H2_BOOT", "H2 GPIO9 strap pull-up"),
    ("R5", "R", "10k", V, "H2_GPIO8", "H2 GPIO8 strap pull-up (download mode needs it high)"),
    ("R6", "R", "1k", "LED_K", G, "LED current (~1.3 mA)"),
    ("R7", "R", "100", "STM_TX_W", "STM_TX", "series: STM32 TX -> C5"),
    ("R8", "R", "100", "STM_RX", "STM_RX_W", "series: C5 -> STM32 RX"),
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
